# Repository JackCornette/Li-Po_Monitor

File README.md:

# Li-Po_Monitor
Custom Voltage and Current LiPo monitor PCB with SPI-CAN Circuit, LCD Display and piezo buzzer. Current is measured via through-hole Hall-Effect sensor with an analog output while voltage is measured in each Li-Po cell using an extended ADC IC. This was designed to monitor the Li-Po Batteries used on the Sooner Rover Team and facilitate simple integration into the CAN-Bus. 

## Parts List
- Seeed Studio XIAO mcu
- MCP3208 ADC Extension IC (SPI)
- SSD1306 LCD Display (128x64, SPI)
- WCS1700 35A Current Sensor
- MCP2515 CAN Controller (SPI)
- MAX3051 CAN Transceiver
- 8 MHz Crystal Oscillator
- LM397 Comparator
- BZV5583v3 Zener Diode
- BS108 MOSFET
- 0805 SMD Resistors
- 0805 SMD Capacitors
- 0805 LEDs
- Piezo Buzzer
- 2.54 mm Pin Headers/ Connectors
- 1x2 Screw Terminal

## Schematic

## PCB Design

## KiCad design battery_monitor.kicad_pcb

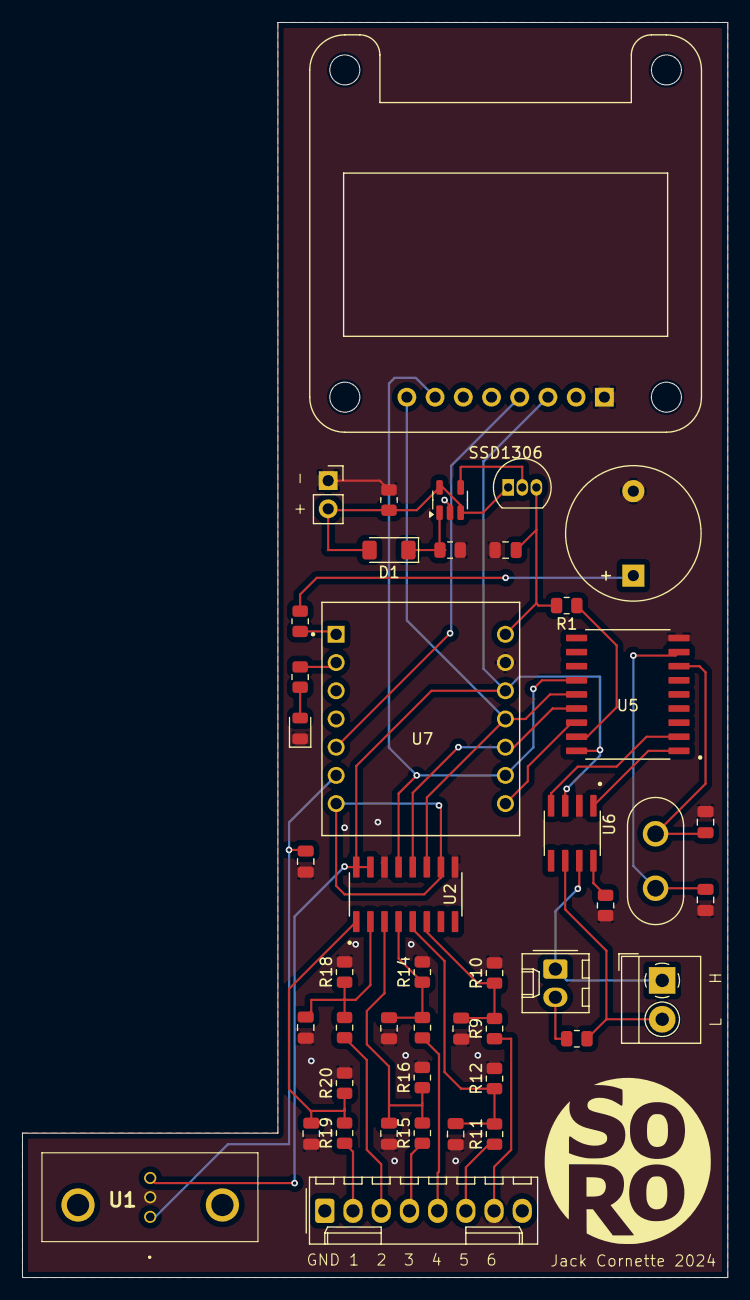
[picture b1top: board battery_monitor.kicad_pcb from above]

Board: 2 copper layers, 63.5 x 113.0 mm, 44 parts (0 on the bottom side), 35 nets.

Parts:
BZ1: Buzzer; Buzzer_12x9.5RM7.6
C1, C2: 22pF; C_0805_2012Metric
C3, C4, C5, C6, C7, C8, C9, C10: 0.1uF; C_0805_2012Metric
D1: BZV55B3V3; D_MiniMELF
D2: LED; LED_0805_2012Metric
J1: Conn_01x07_Pin; Molex_KK-254_AE-6410-08A_1x08_P2.54mm_Vertical
J2: Screw_Terminal; TerminalBlock_4Ucon_1x02_P3.50mm_Horizontal
J3: Conn_01x02_Pin; Molex_KK-254_AE-6410-02A_1x02_P2.54mm_Vertical
Q1: BS108; TO-92_Inline
R1, R4: 10k; R_0805_2012Metric
R2, R3, R9, R10, R11, R12, R13, R14, R15, R16, R17, R18, R19, R20: R_Small_US; R_0805_2012Metric
R5: 100k; R_0805_2012Metric
R6: 120; R_0805_2012Metric
R7: 100; R_0805_2012Metric
SSD1306: Adafruit_SSD1306
U1: WCS1700
U2: MCP3208; SOIC127P600X175-16N
U3: LM397; SOT-23-5
U4: Crystal_Oscillator_8MHz; Crystal_HC50_Vertical
U5: MCP2515-xSO; SOIC127P1030X265-18N
U6: MAX3051; SOIC127P600X175-8N
U7: 102010388; MODULE_102010388

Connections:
+3V3: SSD1306.3, U1.3 (VDD), U2.15 (Vref), U2.16 (Vdd), U5.18 (VDD), U6.3 (VDD), U7.12 (3V3)
+BATT: D1.2 (A), J1.3, Q1.1 (D), R4.1, U3.3 (+), U3.5 (V+)
-BATT: BZ1.2 (-), C1.2, C2.2, C3.1, C4.2, C5.2, C6.2, C7.2, C8.2, C9.2, C10.1, D2.1 (K), J1.1, R4.2, R5.2, R7.2, R10.2, R12.2, R14.2, R16.2, R18.2, R20.2, SSD1306.1, U1.2 (GND), U2.9 (DGND), U2.14 (AGND), U3.2 (V-), U5.9 (VSS), U6.2 (GND), U7.13 (GND)
/A0: C4.1, R19.2, R20.1, U2.1 (CH0)
/A1: C5.1, R17.2, R18.1, U2.2 (CH1)
/A2: C6.1, R15.2, R16.1, U2.3 (CH2)
/A3: C7.1, R13.2, R14.1, U2.4 (CH3)
/A4: C8.1, R11.2, R12.1, U2.5 (CH4)
/A5: C9.1, R9.2, R10.1, U2.6 (CH5)
/CS1: U5.16 (~CS), U7.8 (PB09_A7_D7_RX)
/CS2: U2.10 (~CS/SHDN), U7.7 (PB08_A6_D6_TX)
/Current: C10.2, U1.1 (OUTPUT), U7.6 (PA9_A5_D5_SCL)
/Display: SSD1306.4, U7.5 (PA8_A4_D4_SDA)
/MISO: U2.12 (Dout), U5.15 (SO), U7.10 (PA5_A9_D9_MISO)
/MOSI: SSD1306.8, U2.11 (Din), U5.14 (SI), U7.11 (PA6_A10_D10_MOSI)
/SCK: SSD1306.7, U2.13 (CLK), U5.13 (SCK), U7.9 (PA7_A8_D8_SCK)
unnamed: BZ1.1 (+), R3.1
unnamed: D1.1 (K), R7.1, U3.1 (-)
unnamed: D2.2 (A), R2.2
unnamed: J1.2, R19.1
unnamed: J1.4, R13.1, R15.1
unnamed: J1.6, R11.1
unnamed: J2.1, J3.1, U6.7 (CANH)
unnamed: J2.2, R6.2, U6.6 (CANL)
unnamed: J3.2, R6.1
unnamed: Q1.2 (G), U3.4
unnamed: C2.1, U4.2, U5.8 (OSC1)
unnamed: C1.1, U4.1, U5.7 (OSC2)
unnamed: U5.2 (RXCAN), U6.4 (RXD)
unnamed: U5.1 (TXCAN), U6.1 (TXD)
unnamed: R1.1, U5.17 (~RESET)
unnamed: R5.1, U6.8 (RS)
unnamed: R3.2, U7.1 (PA02_A0_D0)
unnamed: R2.1, U7.2 (PA4_A1_D1)
VCC: C3.2, Q1.3 (S), R1.2, U7.14 (5V)

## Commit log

2024-08-26 Update repo with project details
